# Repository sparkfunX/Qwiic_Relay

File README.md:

SparkFun Qwiic Relay
========================================

[*SparkX Qwiic Relay (SPX-14668)*](https://www.sparkfun.com/products/14668)

Ever wanted to control something that consumes a lot of current? Don't want to hassle with isolating high voltage from your Arduino? Now you don't have to with the Qwiic Relay! This I2C device is allows you to control the Relay with simple I2C commands. You can check the status of the relay and even change the address on the fly, allowing you to control multiple Qwiic Relays!

The Qwiic Relay can handle 5.5 Amps and up to 120 VAC-- perfect for large inductive loads like DC motors or a blender.

The Qwiic Relay comes fully assembled and uses the simple [Qwiic](https://www.sparkfun.com/qwiic) interface. No soldering, no voltage translation, no figuring out which pin is SDA or SCL, just plug and go!

Worried about interacting with Mains (110VAC)? Consider looking at the [IoT Power Relay](https://www.sparkfun.com/products/14236). 

Repository Contents
-------------------

* **/Documents** - Datasheets
* **/Firmware** - Latest firmware and examples. 
* **/Hardware** - Eagle design files (.brd, .sch)

License Information
-------------------

This product is _**open source**_! 

Please review the LICENSE.md file for license information. 

If you have any questions or concerns on licensing, please contact techsupport@sparkfun.com.

Please use, reuse, and modify these files as you see fit. Please maintain attribution to SparkFun Electronics and release under the same license.

Distributed as-is; no warranty is given.

- Your friends at SparkFun.

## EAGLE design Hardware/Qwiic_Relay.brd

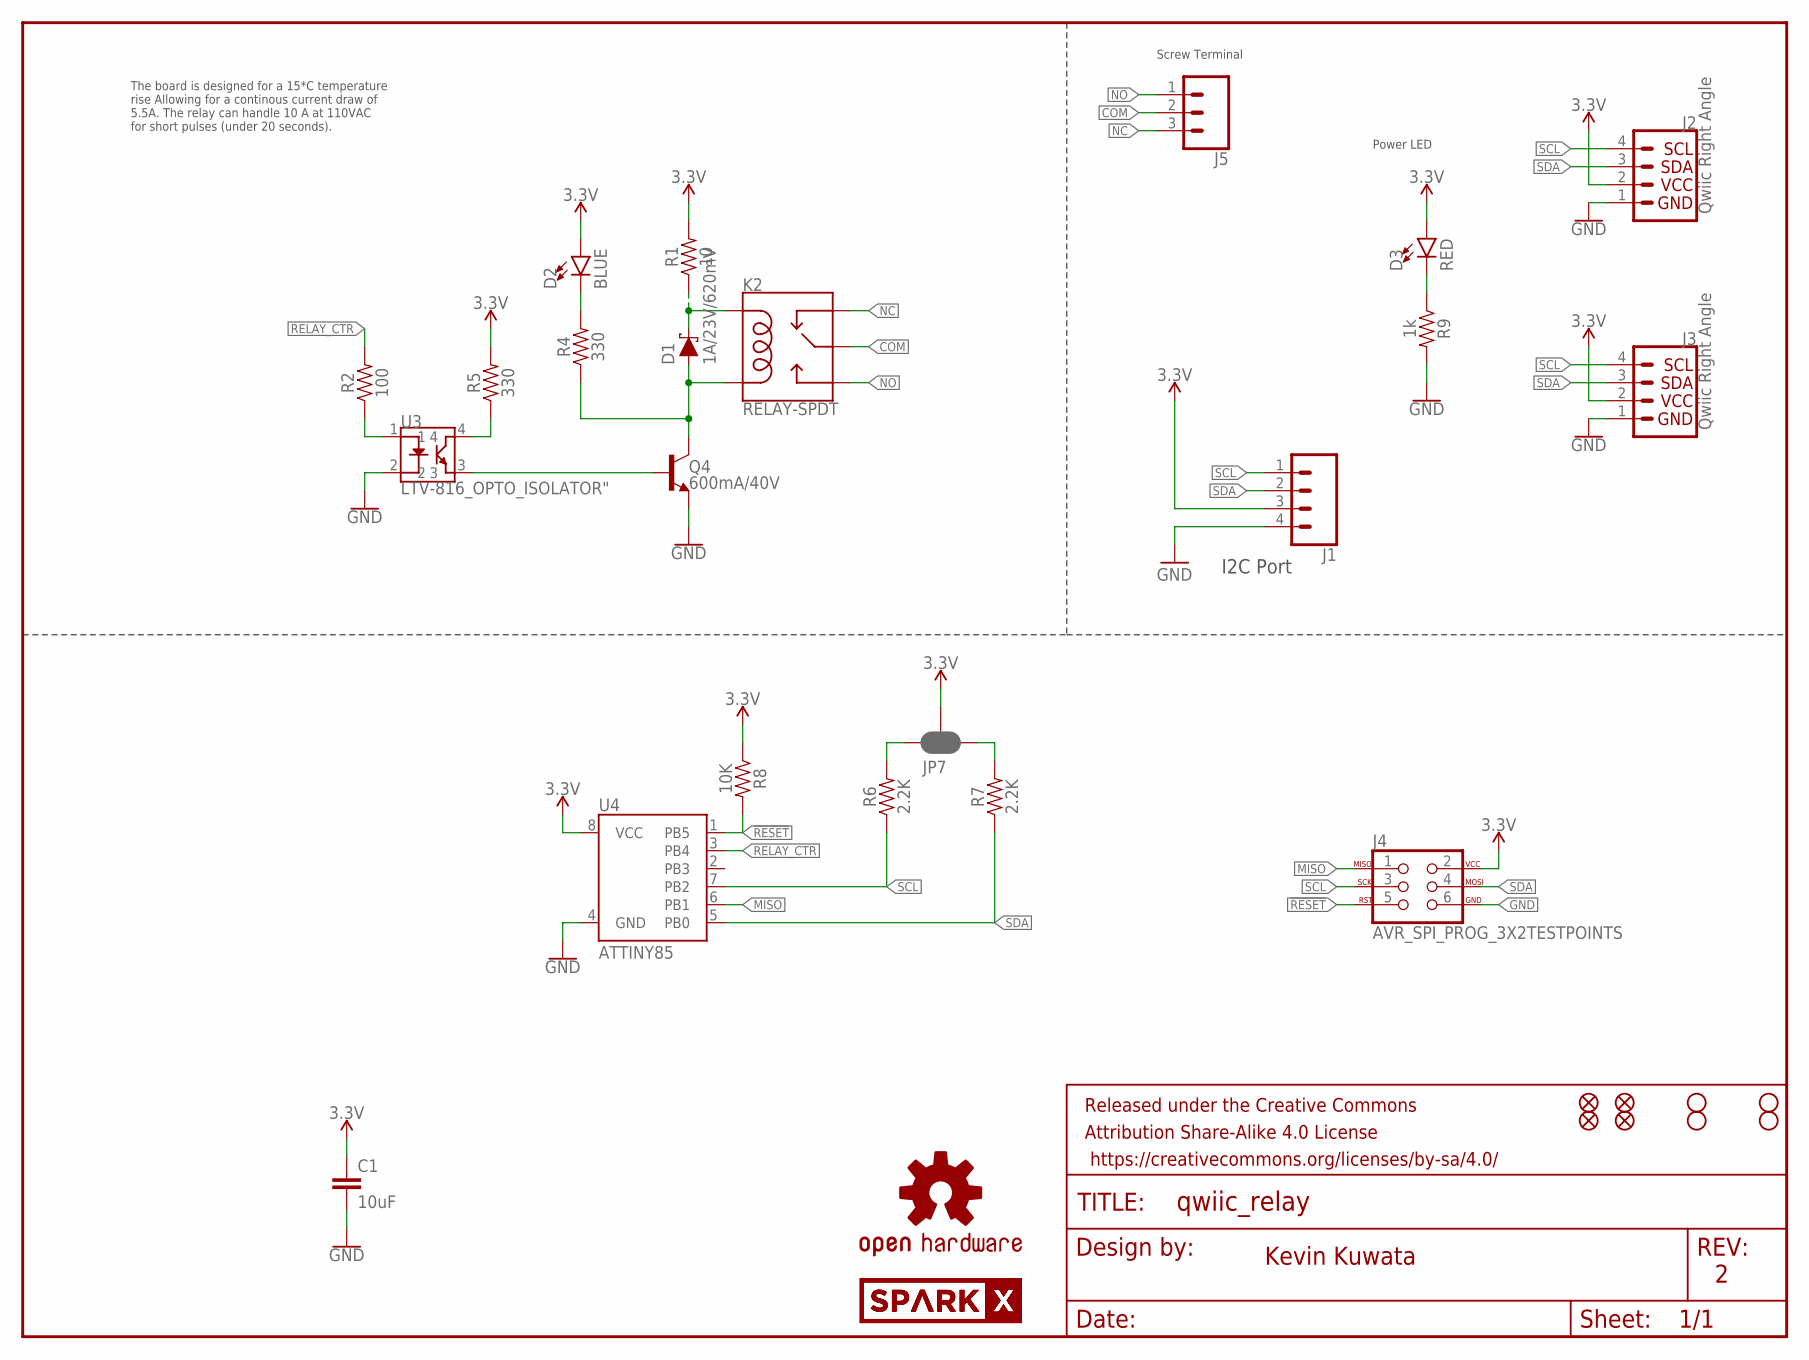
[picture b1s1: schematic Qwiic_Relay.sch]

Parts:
C1: 10uF; 0603
D1: 1A/23V/620mV; SOD-323
D2: BLUE; LED-0603
D3: RED; LED-0603
FRAME1: FRAME-LETTER; CREATIVE_COMMONS
J1: CONN_041X04_NO_SILK; 1X04_NO_SILK
J2, J3: Qwiic Right Angle; 1X04_1MM_RA
J4: AVR_SPI_PROG_3X2TESTPOINTS; 2X3_TEST_POINTS
J5: CONN_03-SCREW-5MM; SCREWTERMINAL-5MM-3
JP1, JP3, JP4, JP5: STAND-OFF
JP2, JP6, JP8, JP9: FIDUCIALUFIDUCIAL; MICRO-FIDUCIAL
JP7: JUMPER-SMT_3_2-NC_PASTE_SILK; SMT-JUMPER_3_2-NC_PASTE_SILK
K2: RELAY-SPDT; RELAY_G5LE
LOGO1: OSHW-LOGOMINI; OSHW-LOGO-MINI
Q4: 600mA/40V; SOT23-3
R1: 10; 0603
R2: 100; 0603
R4, R5: 330; 0603
R6, R7: 2.2K; 0603
R8: 10K; 0603
R9: 1k; 0603
U3: LTV-816_OPTO_ISOLATOR"; LTV-816_4PIN_DIP
U4: ATTINY85
U$3, U$4: SPARKX-LOGO4; SPARKX-MEDIUM

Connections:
3.3V: C1.1, D2.A, D3.A, J1.3, J2.2, J3.2, J4.2, JP7.2, R1.2, R5.2, R8.1, U4.8 (VCC)
!RESET: J4.5, R8.2, U4.1 (PB5)
COM: J5.2, K2.1 (MAIN)
GND: C1.2, J1.4, J2.1, J3.1, J4.6, Q4.2 (E), R9.2, U3.2, U4.4 (GND)
MISO: J4.1, U4.6 (PB1)
unnamed: Q4.1 (B), U3.3
unnamed: D1.A, K2.5 (COIL2), Q4.3 (C), R4.1
unnamed: R2.1, U3.1
unnamed: JP7.1, R7.2
unnamed: D1.C, K2.2 (COIL1), R1.1
unnamed: D2.C, R4.2
unnamed: R5.1, U3.4
unnamed: JP7.3, R6.2
unnamed: D3.C, R9.1
NC: J5.3, K2.4 (NC)
NO: J5.1, K2.3 (NO)
RELAY_CTR: R2.2, U4.3 (PB4)
SCL: J1.1, J2.4, J3.4, J4.3, R6.1, U4.7 (PB2)
SDA: J1.2, J2.3, J3.3, J4.4, R7.1, U4.5 (PB0)

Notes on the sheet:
Kevin Kuwata
Power LED
Screw Terminal
I2C Port
The board is designed for a 15*C temperature rise Allowing for a continous current draw of 5.5A. The relay can handle 10 A at 110VAC for short pulses (under 20 seconds).

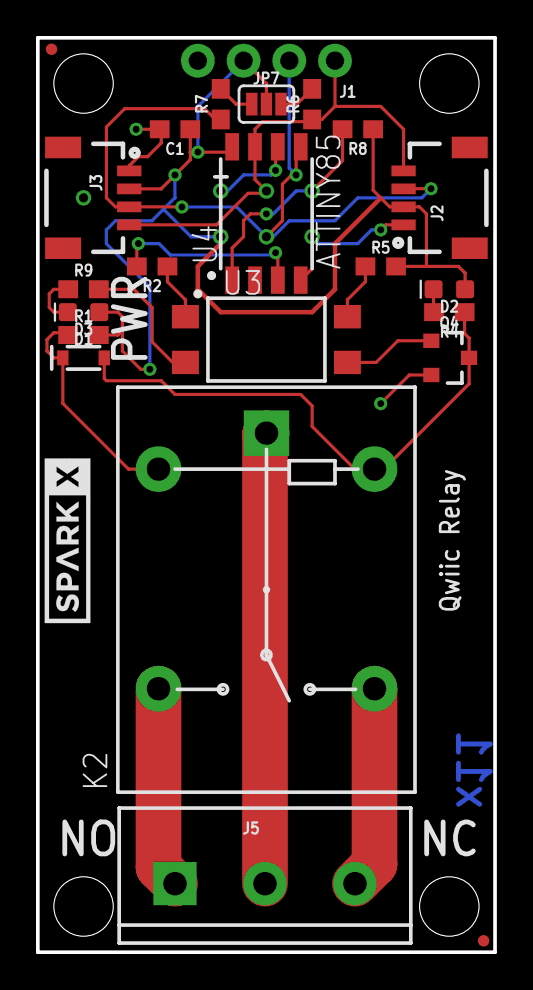
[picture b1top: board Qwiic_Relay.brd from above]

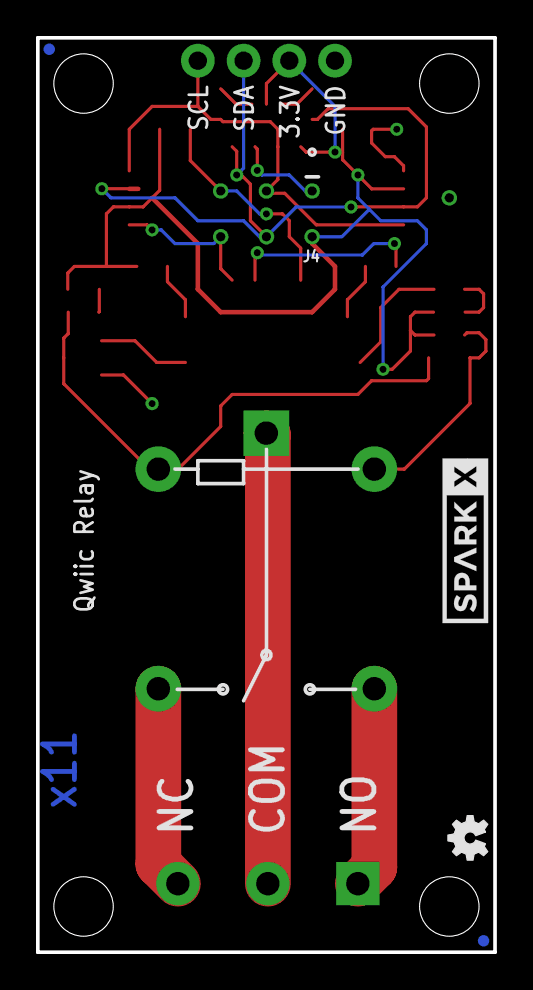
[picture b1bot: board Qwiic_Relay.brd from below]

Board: 2 copper layers, 25.4 x 50.8 mm, 34 parts (5 on the bottom side), 19 nets.

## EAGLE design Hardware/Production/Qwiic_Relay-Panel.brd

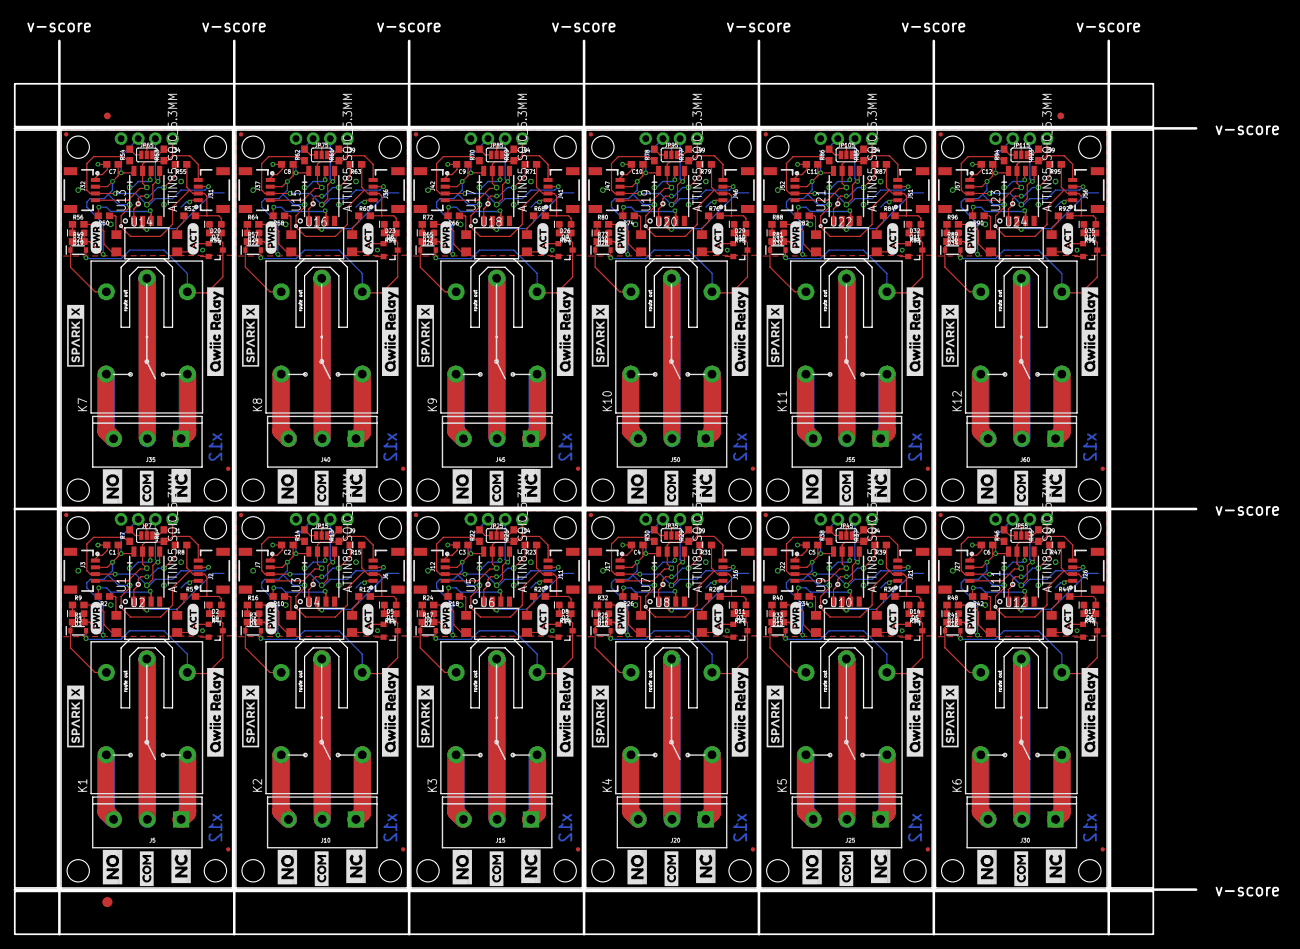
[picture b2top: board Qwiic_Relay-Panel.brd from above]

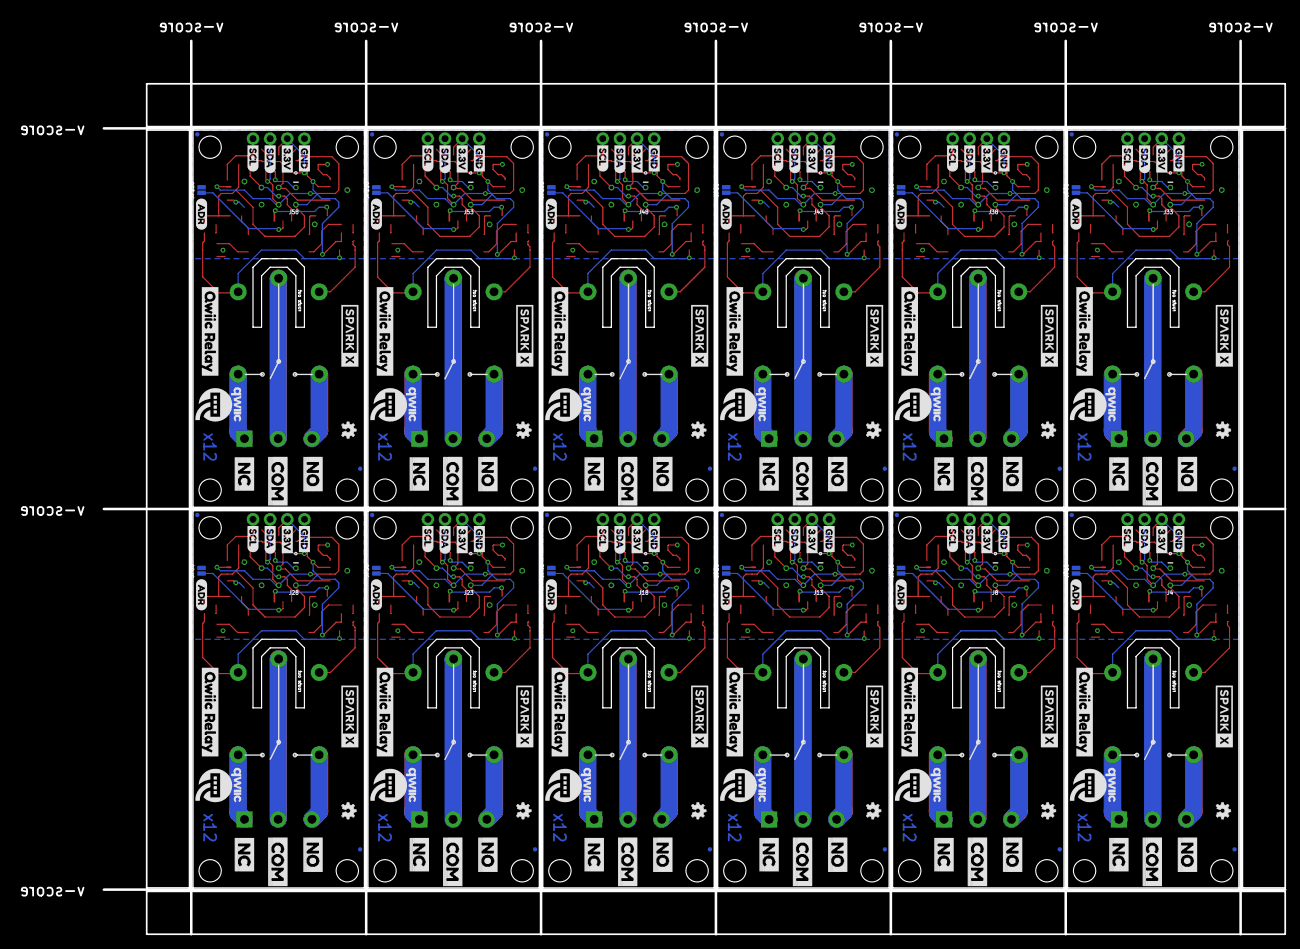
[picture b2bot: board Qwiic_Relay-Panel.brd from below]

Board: 2 copper layers, 188.2 x 136.2 mm, 603 parts (192 on the bottom side), 240 nets.

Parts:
C1, C2, C3, C4, C5, C6, C7, C8, C9, C10, C11, C12: 10uF; 0603
D1, D4, D7, D10, D13, D16, D19, D22, D25, D28, D31, D34: 1A/23V/620mV; SOD-323
D2, D5, D8, D11, D14, D17, D20, D23, D26, D29, D32, D35: BLUE; LED-0603
D3, D6, D9, D12, D15, D18, D21, D24, D27, D30, D33, D36: RED; LED-0603
E$1, E$2: FIDUCIAL-1X2
E$3: FIDUCIAL-1.5X3
J1, J9, J14, J19, J24, J29, J34, J39, J44, J49, J54, J59: 1X04_NO_SILK
J2, J3, J6, J7, J11, J12, J16, J17, J21, J22, J26, J27, J31, J32, J36, J37, J41, J42, J46, J47, J51, J52, J56, J57: Qwiic Right Angle; 1X04_1MM_RA
J4, J8, J13, J18, J23, J28, J33, J38, J43, J48, J53, J58: AVR_SPI_PROG_3X2TESTPOINTS; 2X3_TEST_POINTS
J5, J10, J15, J20, J25, J30, J35, J40, J45, J50, J55, J60: SCREWTERMINAL-5MM-3
JP1, JP3, JP4, JP5, JP11, JP12, JP16, JP17, JP21, JP22, JP26, JP27, JP31, JP32, JP36, JP37, JP41, JP42, JP46, JP47, JP51, JP52, JP56, JP57, JP61, JP62, JP66, JP67, JP71, JP72, JP76, JP77, JP81, JP82, JP86, JP87, JP91, JP92, JP96, JP97, JP101, JP102, JP106, JP107, JP111, JP112, JP116, JP117: STAND-OFF
JP2, JP6, JP8, JP9, JP13, JP14, JP18, JP19, JP23, JP24, JP28, JP29, JP33, JP34, JP38, JP39, JP43, JP44, JP48, JP49, JP53, JP54, JP58, JP59, JP63, JP64, JP68, JP69, JP73, JP74, JP78, JP79, JP83, JP84, JP88, JP89, JP93, JP94, JP98, JP99, JP103, JP104, JP108, JP109, JP113, JP114, JP118, JP119: FIDUCIALUFIDUCIAL; MICRO-FIDUCIAL
JP7, JP15, JP25, JP35, JP45, JP55, JP65, JP75, JP85, JP95, JP105, JP115: SMT-JUMPER_3_2-NC_PASTE_SILK
JP10, JP20, JP30, JP40, JP50, JP60, JP70, JP80, JP90, JP100, JP110, JP120: JUMPER-SMT_2_NO_NO-SILK; SMT-JUMPER_2_NO_NO-SILK
K1, K2, K3, K4, K5, K6, K7, K8, K9, K10, K11, K12: RELAY_SPDT_1C
LOGO1, LOGO2, LOGO3, LOGO4, LOGO5, LOGO6, LOGO7, LOGO8, LOGO9, LOGO10, LOGO11, LOGO12: OSHW-LOGOMINI; OSHW-LOGO-MINI
Q1, Q2, Q3, Q4, Q5, Q6, Q7, Q8, Q9, Q10, Q11, Q12: 600mA/40V; SOT23-3
R1, R3, R17, R25, R33, R41, R49, R57, R65, R73, R81, R89: 10; 0603
R2, R10, R18, R26, R34, R42, R50, R58, R66, R74, R82, R90: 100; 0603
R4, R5, R11, R12, R19, R20, R27, R28, R35, R36, R43, R44, R51, R52, R59, R60, R67, R68, R75, R76, R83, R84, R91, R92: 330; 0603
R6, R7, R13, R14, R21, R22, R29, R30, R37, R38, R45, R46, R53, R54, R61, R62, R69, R70, R77, R78, R85, R86, R93, R94: 2.2K; 0603
R8, R15, R23, R31, R39, R47, R55, R63, R71, R79, R87, R95: 10K; 0603
R9, R16, R24, R32, R40, R48, R56, R64, R72, R80, R88, R96: 1k; 0603
U1, U3, U5, U7, U9, U11, U13, U15, U17, U19, U21, U23: ATTIN85_SOIC_5.3MM; ATTINY85
U2, U4, U6, U8, U10, U12, U14, U16, U18, U20, U22, U24: OPTO_ISOLATOR; 4PIN_DIP
U$1, U$36, U$54, U$72, U$90, U$108, U$126, U$144, U$162, U$180, U$198, U$216: QWIIC-LOGO-MEDIUM
U$2, U$21, U$39, U$57, U$75, U$93, U$111, U$129, U$147, U$165, U$183, U$201: (PWR)
U$3, U$4, U$13, U$14, U$37, U$38, U$55, U$56, U$73, U$74, U$91, U$92, U$109, U$110, U$127, U$128, U$145, U$146, U$163, U$164, U$181, U$182, U$199, U$200: SPARKX-LOGO4; SPARKX-MEDIUM
U$5, U$22, U$40, U$58, U$76, U$94, U$112, U$130, U$148, U$166, U$184, U$202: SCL
U$6, U$23, U$41, U$59, U$77, U$95, U$113, U$131, U$149, U$167, U$185, U$203: SDA
U$7, U$24, U$42, U$60, U$78, U$96, U$114, U$132, U$150, U$168, U$186, U$204: 3.3V
U$8, U$25, U$43, U$61, U$79, U$97, U$115, U$133, U$151, U$169, U$187, U$205: GND
U$9, U$32, U$50, U$68, U$86, U$104, U$122, U$140, U$158, U$176, U$194, U$212: (ADR)
U$10, U$26, U$44, U$62, U$80, U$98, U$116, U$134, U$152, U$170, U$188, U$206: ACT5
U$11, U$18, U$30, U$34, U$48, U$52, U$66, U$70, U$84, U$88, U$102, U$106, U$120, U$124, U$138, U$142, U$156, U$160, U$174, U$178, U$192, U$196, U$210, U$214: NO2
U$12, U$33, U$51, U$69, U$87, U$105, U$123, U$141, U$159, U$177, U$195, U$213: COM7
U$15, U$16, U$27, U$28, U$45, U$46, U$63, U$64, U$81, U$82, U$99, U$100, U$117, U$118, U$135, U$136, U$153, U$154, U$171, U$172, U$189, U$190, U$207, U$208: QWIIC_RELAY1
U$17, U$20, U$29, U$35, U$47, U$53, U$65, U$71, U$83, U$89, U$101, U$107, U$119, U$125, U$137, U$143, U$155, U$161, U$173, U$179, U$191, U$197, U$209, U$215: NC3
U$19, U$31, U$49, U$67, U$85, U$103, U$121, U$139, U$157, U$175, U$193, U$211: COM4

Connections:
3.3V: C1.1, D2.A, D3.A, J1.3, J2.2, J3.2, J4.2, JP7.2, R1.2, R5.2, R8.1, U1.8
3.3V1: C2.1, D5.A, D6.A, J6.2, J7.2, J8.2, J9.3, JP15.2, R3.2, R12.2, R15.1, U3.8
3.3V2: C3.1, D8.A, D9.A, J11.2, J12.2, J13.2, J14.3, JP25.2, R17.2, R20.2, R23.1, U5.8
3.3V3: C4.1, D11.A, D12.A, J16.2, J17.2, J18.2, J19.3, JP35.2, R25.2, R28.2, R31.1, U7.8
3.3V4: C5.1, D14.A, D15.A, J21.2, J22.2, J23.2, J24.3, JP45.2, R33.2, R36.2, R39.1, U9.8
3.3V5: C6.1, D17.A, D18.A, J26.2, J27.2, J28.2, J29.3, JP55.2, R41.2, R44.2, R47.1, U11.8
3.3V6: C7.1, D20.A, D21.A, J31.2, J32.2, J33.2, J34.3, JP65.2, R49.2, R52.2, R55.1, U13.8
3.3V7: C8.1, D23.A, D24.A, J36.2, J37.2, J38.2, J39.3, JP75.2, R57.2, R60.2, R63.1, U15.8
3.3V8: C9.1, D26.A, D27.A, J41.2, J42.2, J43.2, J44.3, JP85.2, R65.2, R68.2, R71.1, U17.8
3.3V9: C10.1, D29.A, D30.A, J46.2, J47.2, J48.2, J49.3, JP95.2, R73.2, R76.2, R79.1, U19.8
3.3V10: C11.1, D32.A, D33.A, J51.2, J52.2, J53.2, J54.3, JP105.2, R81.2, R84.2, R87.1, U21.8
3.3V11: C12.1, D35.A, D36.A, J56.2, J57.2, J58.2, J59.3, JP115.2, R89.2, R92.2, R95.1, U23.8
!RESET: J4.5, R8.2, U1.1
!RESET1: J8.5, R15.2, U3.1
!RESET2: J13.5, R23.2, U5.1
!RESET3: J18.5, R31.2, U7.1
!RESET4: J23.5, R39.2, U9.1
!RESET5: J28.5, R47.2, U11.1
!RESET6: J33.5, R55.2, U13.1
!RESET7: J38.5, R63.2, U15.1
!RESET8: J43.5, R71.2, U17.1
!RESET9: J48.5, R79.2, U19.1
!RESET10: J53.5, R87.2, U21.1
!RESET11: J58.5, R95.2, U23.1
COM: J5.2, K1.1
COM1: J10.2, K2.1
COM2: J15.2, K3.1
COM3: J20.2, K4.1
COM4: J25.2, K5.1
COM5: J30.2, K6.1
COM6: J35.2, K7.1
COM7: J40.2, K8.1
COM8: J45.2, K9.1
COM9: J50.2, K10.1
COM10: J55.2, K11.1
COM11: J60.2, K12.1
GND: C1.2, J1.4, J2.1, J3.1, J4.6, JP10.2, Q4.2, R9.2, U1.4, U2.2
GND1: C2.2, J6.1, J7.1, J8.6, J9.4, JP20.2, Q1.2, R16.2, U3.4, U4.2
GND2: C3.2, J11.1, J12.1, J13.6, J14.4, JP30.2, Q2.2, R24.2, U5.4, U6.2
GND3: C4.2, J16.1, J17.1, J18.6, J19.4, JP40.2, Q3.2, R32.2, U7.4, U8.2
GND4: C5.2, J21.1, J22.1, J23.6, J24.4, JP50.2, Q5.2, R40.2, U9.4, U10.2
GND5: C6.2, J26.1, J27.1, J28.6, J29.4, JP60.2, Q6.2, R48.2, U11.4, U12.2
GND6: C7.2, J31.1, J32.1, J33.6, J34.4, JP70.2, Q7.2, R56.2, U13.4, U14.2
GND7: C8.2, J36.1, J37.1, J38.6, J39.4, JP80.2, Q8.2, R64.2, U15.4, U16.2
GND8: C9.2, J41.1, J42.1, J43.6, J44.4, JP90.2, Q9.2, R72.2, U17.4, U18.2
GND9: C10.2, J46.1, J47.1, J48.6, J49.4, JP100.2, Q10.2, R80.2, U19.4, U20.2
GND10: C11.2, J51.1, J52.1, J53.6, J54.4, JP110.2, Q11.2, R88.2, U21.4, U22.2
GND11: C12.2, J56.1, J57.1, J58.6, J59.4, JP120.2, Q12.2, R96.2, U23.4, U24.2
MISO: J4.1, U1.6
MISO1: J8.1, U3.6
MISO2: J13.1, U5.6
MISO3: J18.1, U7.6
MISO4: J23.1, U9.6
MISO5: J28.1, U11.6
MISO6: J33.1, U13.6
MISO7: J38.1, U15.6
MISO8: J43.1, U17.6
MISO9: J48.1, U19.6
MISO10: J53.1, U21.6
MISO11: J58.1, U23.6
unnamed: Q4.1, U2.3
unnamed: D1.A, K1.5, Q4.3, R4.1
unnamed: R2.1, U2.1
unnamed: JP7.1, R7.2
unnamed: JP10.1, U1.2
unnamed: D4.A, K2.5, Q1.3, R11.1
unnamed: D1.C, K1.2, R1.1
unnamed: D2.C, R4.2
unnamed: R5.1, U2.4
unnamed: JP7.3, R6.2
unnamed: D4.C, K2.2, R3.1
unnamed: D5.C, R11.2
unnamed: D3.C, R9.1
unnamed: R12.1, U4.4
unnamed: JP15.1, R14.2
unnamed: JP15.3, R13.2
unnamed: D6.C, R16.1
unnamed: R10.1, U4.1
unnamed: Q1.1, U4.3
unnamed: JP20.1, U3.2
unnamed: D7.A, K3.5, Q2.3, R19.1
unnamed: D7.C, K3.2, R17.1
unnamed: D8.C, R19.2
unnamed: R20.1, U6.4
unnamed: JP25.1, R22.2
unnamed: JP25.3, R21.2
unnamed: D9.C, R24.1
unnamed: R18.1, U6.1
unnamed: Q2.1, U6.3
unnamed: JP30.1, U5.2
unnamed: D10.A, K4.5, Q3.3, R27.1
unnamed: D10.C, K4.2, R25.1
unnamed: D11.C, R27.2
unnamed: R28.1, U8.4
unnamed: JP35.1, R30.2
unnamed: JP35.3, R29.2
unnamed: D12.C, R32.1
unnamed: R26.1, U8.1
unnamed: Q3.1, U8.3
unnamed: JP40.1, U7.2
unnamed: D13.A, K5.5, Q5.3, R35.1
unnamed: D13.C, K5.2, R33.1
unnamed: D14.C, R35.2
unnamed: R36.1, U10.4
unnamed: JP45.1, R38.2
unnamed: JP45.3, R37.2
unnamed: D15.C, R40.1
unnamed: R34.1, U10.1
unnamed: Q5.1, U10.3
unnamed: JP50.1, U9.2
unnamed: D16.A, K6.5, Q6.3, R43.1
unnamed: D16.C, K6.2, R41.1
unnamed: D17.C, R43.2
unnamed: R44.1, U12.4
unnamed: JP55.1, R46.2
unnamed: JP55.3, R45.2
unnamed: D18.C, R48.1
unnamed: R42.1, U12.1
unnamed: Q6.1, U12.3
unnamed: JP60.1, U11.2
unnamed: D19.A, K7.5, Q7.3, R51.1
unnamed: D19.C, K7.2, R49.1
unnamed: D20.C, R51.2
unnamed: R52.1, U14.4
unnamed: JP65.1, R54.2
unnamed: JP65.3, R53.2
unnamed: D21.C, R56.1
unnamed: R50.1, U14.1
unnamed: Q7.1, U14.3
unnamed: JP70.1, U13.2
unnamed: D22.A, K8.5, Q8.3, R59.1
unnamed: D22.C, K8.2, R57.1
unnamed: D23.C, R59.2
unnamed: R60.1, U16.4
unnamed: JP75.1, R62.2
unnamed: JP75.3, R61.2
unnamed: D24.C, R64.1
unnamed: R58.1, U16.1
unnamed: Q8.1, U16.3
unnamed: JP80.1, U15.2
unnamed: D25.A, K9.5, Q9.3, R67.1
unnamed: D25.C, K9.2, R65.1
unnamed: D26.C, R67.2
unnamed: R68.1, U18.4
unnamed: JP85.1, R70.2
unnamed: JP85.3, R69.2
unnamed: D27.C, R72.1
unnamed: R66.1, U18.1
unnamed: Q9.1, U18.3
unnamed: JP90.1, U17.2
unnamed: D28.A, K10.5, Q10.3, R75.1
unnamed: D28.C, K10.2, R73.1
unnamed: D29.C, R75.2
unnamed: R76.1, U20.4
unnamed: JP95.1, R78.2
unnamed: JP95.3, R77.2
unnamed: D30.C, R80.1
unnamed: R74.1, U20.1
unnamed: Q10.1, U20.3
unnamed: JP100.1, U19.2
unnamed: D31.A, K11.5, Q11.3, R83.1
unnamed: D31.C, K11.2, R81.1
unnamed: D32.C, R83.2
unnamed: R84.1, U22.4
unnamed: JP105.1, R86.2
unnamed: JP105.3, R85.2
unnamed: D33.C, R88.1
unnamed: R82.1, U22.1
unnamed: Q11.1, U22.3
unnamed: JP110.1, U21.2
unnamed: D34.A, K12.5, Q12.3, R91.1
unnamed: D34.C, K12.2, R89.1
unnamed: D35.C, R91.2
unnamed: R92.1, U24.4
unnamed: JP115.1, R94.2
unnamed: JP115.3, R93.2
unnamed: D36.C, R96.1
unnamed: R90.1, U24.1
unnamed: Q12.1, U24.3
unnamed: JP120.1, U23.2
NC: J5.1, K1.4
NC1: J10.1, K2.4
NC2: J15.1, K3.4
NC3: J20.1, K4.4
NC4: J25.1, K5.4
NC5: J30.1, K6.4
NC6: J35.1, K7.4
NC7: J40.1, K8.4
NC8: J45.1, K9.4
NC9: J50.1, K10.4
NC10: J55.1, K11.4
NC11: J60.1, K12.4
NO: J5.3, K1.3
NO1: J10.3, K2.3
NO2: J15.3, K3.3
NO3: J20.3, K4.3
NO4: J25.3, K5.3
NO5: J30.3, K6.3
NO6: J35.3, K7.3
NO7: J40.3, K8.3
NO8: J45.3, K9.3
NO9: J50.3, K10.3
NO10: J55.3, K11.3
NO11: J60.3, K12.3
RELAY_CTR: R2.2, U1.3
RELAY_CTR1: R10.2, U3.3
RELAY_CTR2: R18.2, U5.3
RELAY_CTR3: R26.2, U7.3
RELAY_CTR4: R34.2, U9.3
RELAY_CTR5: R42.2, U11.3
RELAY_CTR6: R50.2, U13.3
RELAY_CTR7: R58.2, U15.3
RELAY_CTR8: R66.2, U17.3
RELAY_CTR9: R74.2, U19.3
RELAY_CTR10: R82.2, U21.3
RELAY_CTR11: R90.2, U23.3
SCL: J1.1, J2.4, J3.4, J4.3, R6.1, U1.7
SCL1: J6.4, J7.4, J8.3, J9.1, R13.1, U3.7
SCL2: J11.4, J12.4, J13.3, J14.1, R21.1, U5.7
SCL3: J16.4, J17.4, J18.3, J19.1, R29.1, U7.7
SCL4: J21.4, J22.4, J23.3, J24.1, R37.1, U9.7
SCL5: J26.4, J27.4, J28.3, J29.1, R45.1, U11.7
SCL6: J31.4, J32.4, J33.3, J34.1, R53.1, U13.7
SCL7: J36.4, J37.4, J38.3, J39.1, R61.1, U15.7
SCL8: J41.4, J42.4, J43.3, J44.1, R69.1, U17.7
SCL9: J46.4, J47.4, J48.3, J49.1, R77.1, U19.7
SCL10: J51.4, J52.4, J53.3, J54.1, R85.1, U21.7
SCL11: J56.4, J57.4, J58.3, J59.1, R93.1, U23.7
SDA: J1.2, J2.3, J3.3, J4.4, R7.1, U1.5
SDA1: J6.3, J7.3, J8.4, J9.2, R14.1, U3.5
SDA2: J11.3, J12.3, J13.4, J14.2, R22.1, U5.5
SDA3: J16.3, J17.3, J18.4, J19.2, R30.1, U7.5
SDA4: J21.3, J22.3, J23.4, J24.2, R38.1, U9.5
SDA5: J26.3, J27.3, J28.4, J29.2, R46.1, U11.5
SDA6: J31.3, J32.3, J33.4, J34.2, R54.1, U13.5
SDA7: J36.3, J37.3, J38.4, J39.2, R62.1, U15.5
SDA8: J41.3, J42.3, J43.4, J44.2, R70.1, U17.5
SDA9: J46.3, J47.3, J48.4, J49.2, R78.1, U19.5
SDA10: J51.3, J52.3, J53.4, J54.2, R86.1, U21.5
SDA11: J56.3, J57.3, J58.4, J59.2, R94.1, U23.5

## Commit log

2018-02-26 init
2018-02-26 Adding ignore
2018-02-28 ordered board
2018-03-01 fixed bottom silk dimension
2018-03-21 added Example 1- Basic Control and Example 2- Change Address
2018-03-21 added examples and firmware
2018-03-21 include firmware and examples
2018-03-28 Adding example 5 - check firmware version
2018-03-28 adding changes to firmware, before a fetch
2018-03-28 minor changes to setup() making it clearer for user and forcing a known state of the relay
2018-03-28 minor changes to setup()
2018-03-29 making changes to the firmware from the review, but have proven to be broken going to revert back a commit
2018-03-29 added a testForConnectivity() function which tests in the setup and then freezes if there is no relay attached. Cleaned unnecessary comments
2018-03-29 update example 2. removed comments, and moved test case into setup so that we are not writing to eeprom a billion times
2018-03-29 4th example: cleaned up the comments, used testForConnectivity() in setup,
2018-03-29 changed example 4: to be more concise, removed all extra comments in examples 1, 2, and 4, example 3 is a direct copy of the i2c scanner from arduino playground
2018-04-02 fixed the relay bug where the relay would fail to trigger, I had accidently set up the pinmode twice. I needed to set the relay low not the pinmode low.
2018-04-02 fixed bug when transfering from array based ISR handlers to 2 bytes command / address. the problem was i was servicing the ISR, and checking 2 checks for 1 byte of data, when in reality I need to do 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
2018-04-02 the ISR for Rx event is not making it into my case statement with flag: versionFlag == 1, maybe i need a delay between the write, and request. so the flag has time to change. it is volatile
2018-04-02 worked on adding getting version out of the firmware, changed the onI2C request handler so that i send over [hardcoded] version number. tinyWire doesn't work well with sending more than 1 byte. need 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
2018-04-03 Nate helped cleaned this up quite a bit, removed all flags so code is deterministic, and fixed the firmware float version issue. I call it the Beau trick. Take your high and low bytes, cast one to a 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
2018-04-03 added example 5, cleaend up examples with defines when appropriate, going to merge to master
2018-04-03 deleted redundant example 5 after merge to master
2018-04-03 verfied examples work, merging with master
2018-04-04 Revert "Nate helped cleaned this up quite a bit, removed all flags so code is deterministic, and fixed the firmware float version issue. I call it the Beau trick. Take your high and low bytes, cast o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
    This reverts commit 34565a5c9fb479b53dd11eaa8e6bcc8cf3833fe0.
2018-04-04 reverted back to an older version, then i went through the firmware and corrected the git conflicts, then i compiled. now i'm going to verify the other examples still work before flashing new firmwar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
2018-04-04 this should be merged to master
2018-04-04 Formatting with Arduino
    Formatted code in Arduino IDE. Ready to be merged with master.
2018-04-04 removed unnecessary comment
    removed an unnecessary comment
2018-04-04 cleaned up repo
    cleaned up the folders, fixed file name for example 1.
2018-04-04 updating read me
    added a description want to see what it looks like
2018-04-04 updated repo
    - Removed unnecessary eagle documents
    - added IoT relay as related product
    - included a pdf of the schematic
    - added relay datasheet
2018-04-04 changed iot
    minor grammar
2018-04-04 github and product page match
    making description match product page
2018-04-04 deleted redundant panel filies
2018-04-04 removed typo in read me
2018-04-04 added pdf
    added pdf of schematic into the hardware folder,changed read me, and added more details to the schematic about max currents.
2018-04-05 Adding clearance and cutout
    I added cleraance of 2.5 mm of cleraance from the common pin of the relay to any copper to prevent voltage creep. Also included a cutout in the mill layer to further increase creep distance. I includ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
2018-04-05 minimum spacing
    minimum spacing according to this cacluator http://www.creepage.com/ is 2.4mm. the cutout prevents leakage current. the spcaing prevents arcing
2018-04-05 moved the coil trace outside of the routeout
2018-04-09 Rev 2 and sent to fab
    Revision 2 of the board. (x12)
    added more clearance to the PCB
    added buzzard labels
    added cutout into the dimension layer so that it is exported to GKO
    fixed spacing on the Schematic
    added address jumper to pin 2 of the ATtiny85
2018-04-10 Fixed dimensions and mill lines to appropriate layers.
2018-04-17 implemented external jumper for addressing
    If the external jumper is closed the address is forced to 0x19. If the jumper is open then the eeprom will be read and if blank, the default address 0x18 will be used.
    if the jumper is closed and the address is changed it will be stored in eeprom but the device will not use that address.
2018-04-19 update address jumper
    added address jumper code to be recognized
2018-04-19 switching over to wire.h and attinycore
2018-04-19 confirmed 400khz compatibility
    burning attinycore bootloader is required to get the 400khz i2c to work. the newest relays have the Wire.h compatibility no longer need tinywire.
2018-04-19 fixed buzzard label
    fixed the flipped labels NC and NO. now they match the direction of COM and what the rest of the text orientations
2018-04-20 Small changes to silk and version number
2018-04-20 Adding Qwiic Logo to bottom silk
2018-05-15 Creating Assembly Sheet
2018-05-15 Matching components values
2018-11-20 updated relay to use the sealed version
2018-11-21 updated parts for sparkle parts

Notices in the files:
parts and their libraries:
SparkFun-Capacitors: Licensing: Creative Commons ShareAlike 4.0 International - https://creativecommons.org/licenses/by-sa/4.0
SparkFun-Aesthetics: Released under the Creative Commons Attribution Share-Alike 4.0 License
SparkFun-Aesthetics: https://creativecommons.org/licenses/by-sa/4.0
